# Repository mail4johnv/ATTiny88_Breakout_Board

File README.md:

# ATTiny88 Breakout Board

A compact breakout board for the Microchip/Atmel ATtiny88 microcontroller. This repository contains the KiCad source, PCB/gerber exports, BOM, assembly notes, and example firmware to help you build and use the board.

Status
- Board design: Prototype (update to "Verified" or "Production" as appropriate)
- KiCad project: Hardware/ (KiCad project files)
- Example firmware: /firmware/examples

Quick links
- Hardware (KiCad project & schematics): Hardware/
- BOM: bom/bom.csv
- License: LICENSE (Mozilla Public License 2.0)

Features
- ATtiny88 (28-pin package) breakout to 0.1" headers
- 6-pin AVR ISP programming header
- Power supply decoupling and filter footprints
- Mounting holes for mechanical support

Repository layout
- Hardware/ — KiCad project files, schematics, PCB layouts
- hardware/gerbers/ — Exported Gerber/Drill files
- images/ — photos and pinout image(s)

Quick start (build & test)
1. Inspect schematic: open Hardware/ in KiCad and review the schematic
2. Program & test:
   - Connect a 6-pin AVR ISP to the ISP header.
   - Arduino as ISP (Arduino UNO example):
     - Upload ArduinoISP sketch to UNO.
     - Wire UNO to the board ISP header.
     - In Arduino IDE select correct ATTiny core/board and use "Upload Using Programmer".
   - avrdude example (update programmer type and port):
     - avrdude -c usbtiny -p t88 -P usb -U flash:w:firmware.hex
3. Basic verification:
   - Power the board and run any example assembly

License
This project is released under the Mozilla Public License 2.0 — see LICENSE for full text.

Maintainer
- mail4johnv (GitHub)

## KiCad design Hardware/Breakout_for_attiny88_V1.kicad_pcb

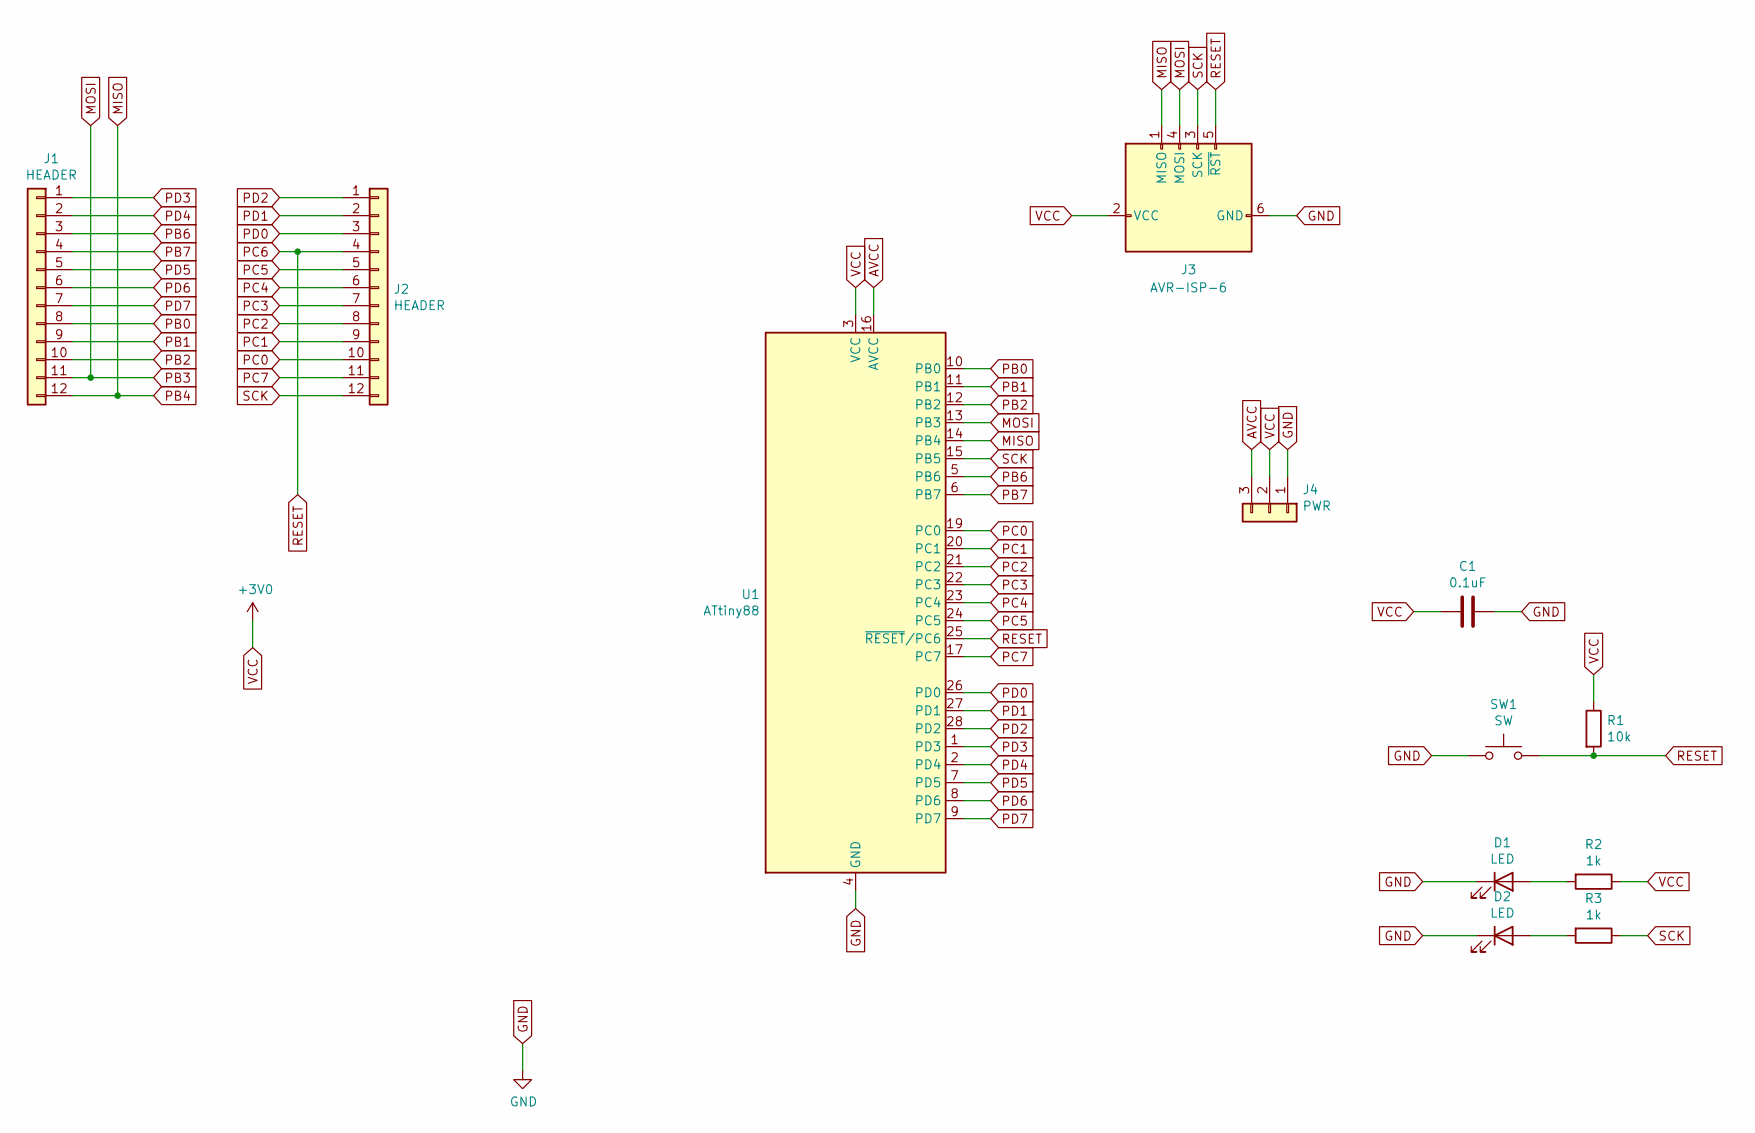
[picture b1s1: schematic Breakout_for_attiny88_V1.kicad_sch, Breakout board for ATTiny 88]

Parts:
C1: 0.1uF; C_0805_2012Metric_Pad1.18x1.45mm_HandSolder
D1, D2: LED; LED_0805_2012Metric_Pad1.15x1.40mm_HandSolder
J1, J2: HEADER; Pin_Header_Straight_1x12_Pitch2.54mm
J3: AVR-ISP-6; IDC-Header_2x03_P2.54mm_Vertical
J4: PWR; Pin_Header_Straight_1x03_Pitch2.54mm
R1: 10k; R_0805_2012Metric_Pad1.20x1.40mm_HandSolder
R2, R3: 1k; R_0805_HandSoldering
SW1: SW; push_button_switch
U1: ATtiny88; QFN45P400X400X100-29N-D

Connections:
AVCC: J4.3, U1.16 (AVCC)
GND: C1.1, D1.1 (K), D2.1 (K), J3.6 (GND), J4.1, SW1.1, SW1.3, U1.4 (GND), U1.18 (GND), U1.29 (GND)
MISO: J1.12, J3.1 (MISO), U1.14 (PB4)
MOSI: J1.11, J3.4 (MOSI), U1.13 (PB3)
unnamed: D1.2 (A), R2.2
unnamed: D2.2 (A), R3.2
PB0: J1.8, U1.10 (PB0)
PB1: J1.9, U1.11 (PB1)
PB2: J1.10, U1.12 (PB2)
PB6: J1.3, U1.5 (PB6)
PB7: J1.4, U1.6 (PB7)
PC0: J2.10, U1.19 (PC0)
PC1: J2.9, U1.20 (PC1)
PC2: J2.8, U1.21 (PC2)
PC3: J2.7, U1.22 (PC3)
PC4: J2.6, U1.23 (PC4)
PC5: J2.5, U1.24 (PC5)
PC6: J2.4, J3.5 (~RST), R1.2, SW1.2, U1.25 (~RESET~/PC6)
PC7: J2.11, U1.17 (PC7)
PD0: J2.3, U1.26 (PD0)
PD1: J2.2, U1.27 (PD1)
PD2: J2.1, U1.28 (PD2)
PD3: J1.1, U1.1 (PD3)
PD4: J1.2, U1.2 (PD4)
PD5: J1.5, U1.7 (PD5)
PD6: J1.6, U1.8 (PD6)
PD7: J1.7, U1.9 (PD7)
SCK: J2.12, J3.3 (SCK), R3.1, U1.15 (PB5)
VCC: C1.2, J3.2 (VCC), J4.2, R1.1, R2.1, U1.3 (VCC)

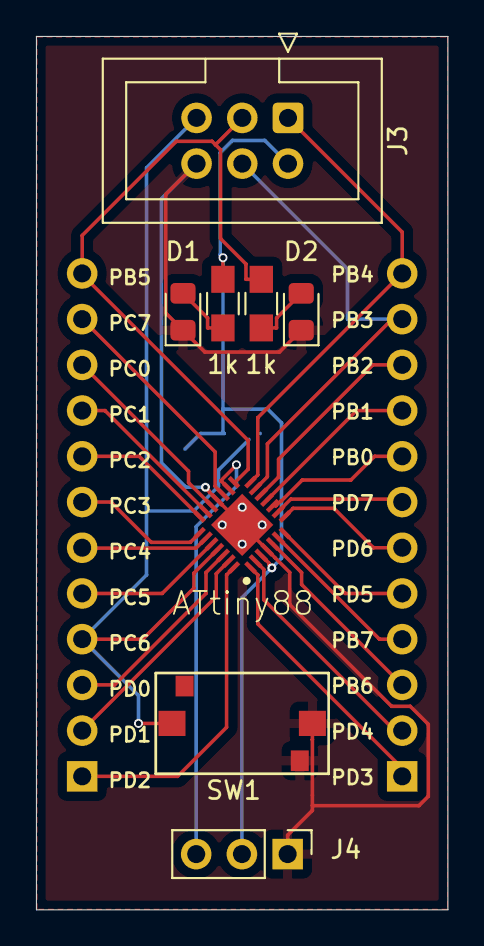
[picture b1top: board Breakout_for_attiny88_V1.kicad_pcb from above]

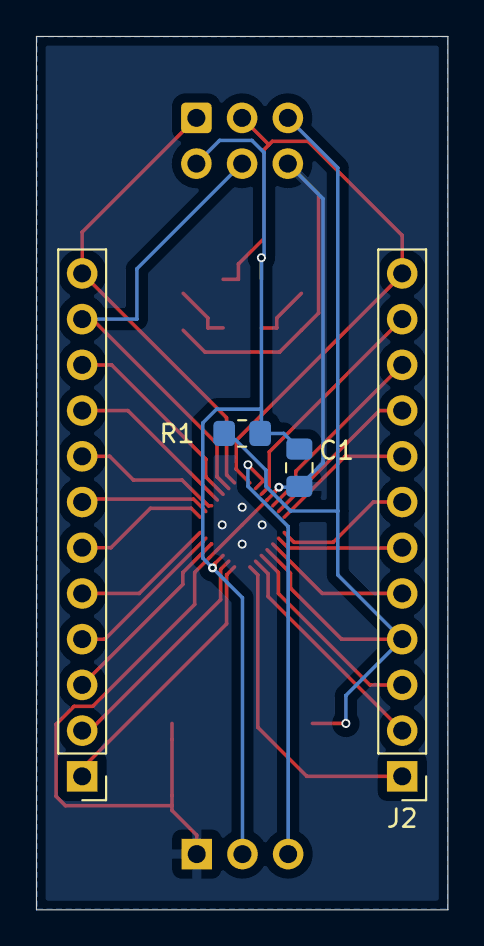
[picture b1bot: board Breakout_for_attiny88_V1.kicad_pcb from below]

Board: 2 copper layers, 22.9 x 48.5 mm, 12 parts (4 on the bottom side), 29 nets.

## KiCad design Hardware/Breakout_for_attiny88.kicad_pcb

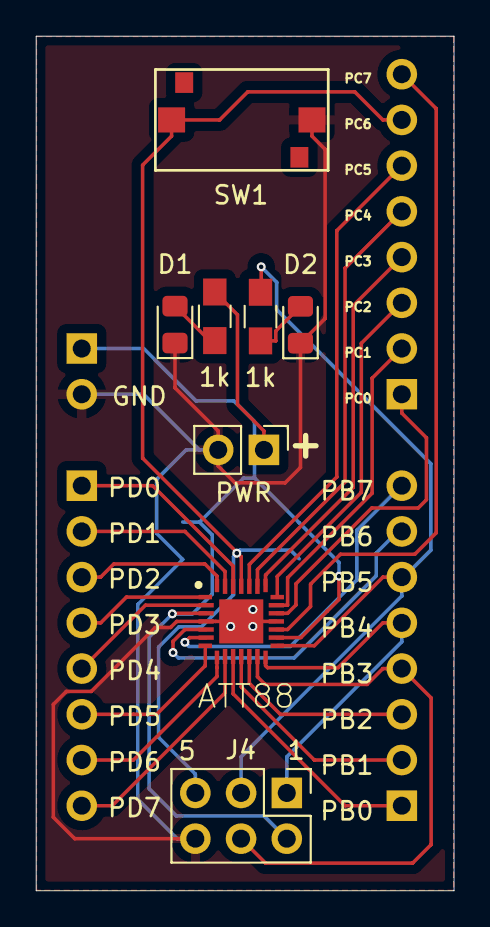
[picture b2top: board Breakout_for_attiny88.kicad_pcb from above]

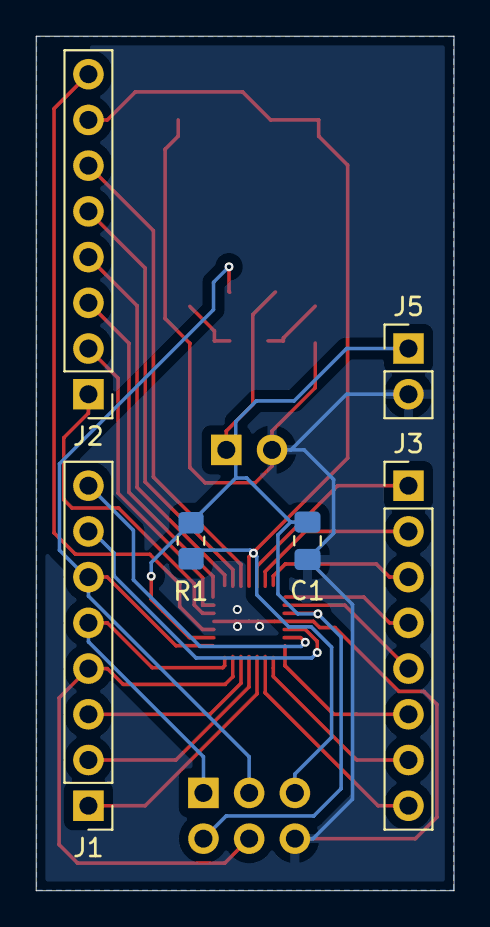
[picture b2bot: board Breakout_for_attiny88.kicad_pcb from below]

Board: 2 copper layers, 23.2 x 47.5 mm, 14 parts (6 on the bottom side), 28 nets.

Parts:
C1: 0.1uF; C_0805_2012Metric_Pad1.18x1.45mm_HandSolder
D1, D2: LED; LED_0805_2012Metric_Pad1.15x1.40mm_HandSolder
J1, J2, J3: Conn_01x08; PinHeader_1x08_P2.54mm_Vertical
J4: AVR-ISP-6; PinHeader_2x03_P2.54mm_Vertical
J5, J6: Conn_01x02; PinHeader_1x02_P2.54mm_Vertical
R1: 10k; R_0805_2012Metric_Pad1.20x1.40mm_HandSolder
R2, R3: 1k; R_0805_HandSoldering
SW1: SW; push_button_switch
U1: ATT88; QFN45P400X400X100-29N-D

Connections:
GND: C1.1, D1.1 (K), D2.1 (K), J4.6 (GND), J5.2, J6.2, SW1.1, U1.4 (GND), U1.18 (GND), U1.29 (GND)
MISO: J1.5, J4.1 (MISO), U1.14 (PB4)
MOSI: J1.4, J4.4 (MOSI), U1.13 (PB3)
unnamed: D1.2 (A), R2.2
unnamed: D2.2 (A), R3.2
PB0: J1.1, U1.10 (PB0)
PB1: J1.2, U1.11 (PB1)
PB2: J1.3, U1.12 (PB2)
PB5: J1.6, J4.3 (SCK), R3.1, U1.15 (PB5)
PB6: J1.7, U1.5 (PB6)
PB7: J1.8, U1.6 (PB7)
PC0: J2.1, U1.19 (PC0)
PC1: J2.2, U1.20 (PC1)
PC2: J2.3, U1.21 (PC2)
PC3: J2.4, U1.22 (PC3)
PC4: J2.5, U1.23 (PC4)
PC5: J2.6, U1.24 (PC5)
PC6: J2.7, J4.5 (~RST), R1.2, SW1.2, U1.25 (~RESET~/PC6)
PC7: J2.8, U1.17 (PC7)
PD0: J3.1, U1.26 (PD0)
PD1: J3.2, U1.27 (PD1)
PD2: J3.3, U1.28 (PD2)
PD3: J3.4, U1.1 (PD3)
PD4: J3.5, U1.2 (PD4)
PD5: J3.6, U1.7 (PD5)
PD6: J3.7, U1.8 (PD6)
PD7: J3.8, U1.9 (PD7)
VCC: C1.2, J4.2 (VCC), J5.1, J6.1, R1.1, R2.1, U1.3 (VCC), U1.16 (AVCC)

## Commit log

2020-12-08 Initial Files
    Kicad Files for breakout board.
2020-12-09 add filled zone on both sides.
2020-12-09 add filled zone
2020-12-09 modified Ground plane
2020-12-09 added 3d view
2020-12-11 Added_New_PCB
2020-12-15 pcb changed to add port pins on each header
2025-10-22 Updated README.md
    Expanded the README to provide more details about the ATTiny88 breakout board, including features, repository layout, quick start instructions, and licensing information.
